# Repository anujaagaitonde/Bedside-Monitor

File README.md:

# LifeLine

LifeLine is a low-cost Internet-of-Things vital sign monitor with real-time illness prediction which allows doctors to monitor several patients at once from a remote location. Custom circuitry interfaces sensors to measure the patient's vital signs with any Raspberry Pi. Sensor data is displayed live on a bedside monitor and is live-streamed to a cloud-based database. A webapp allows doctors to monitor all their patients live, as well as viewing patient history over the past 24 hours. Sensor data is processed in real-time by a machine learning algorithm to detect and predict a critical event in the patient's status, which is relayed to the doctor via an instant notification in the webapp.

## Documentation

For further information about this project, visit our [wiki](https://github.com/anujaagaitonde/Bedside-Monitor/wiki):
* [1. Home](https://github.com/anujaagaitonde/Bedside-Monitor/wiki/1.-Home)
* [2. Product Design History](https://github.com/anujaagaitonde/Bedside-Monitor/wiki/2.-Product-Design-History)
* [2.1 Hardware and Firmware](https://github.com/anujaagaitonde/Bedside-Monitor/wiki/2.1-Hardware-and-Firmware)
* [2.2 Web App](https://github.com/anujaagaitonde/Bedside-Monitor/wiki/2.2-Web-App)
* [2.4 Deep Learning Model](https://github.com/anujaagaitonde/Bedside-Monitor/wiki/2.3-Deep-Learning-Model)
* [3. Meeting Records](https://github.com/anujaagaitonde/Bedside-Monitor/wiki/3.-Meeting-Records)
* [4. Innovation](https://github.com/anujaagaitonde/Bedside-Monitor/wiki/4.-Innovation)
* [5. Report of Ethical Consequences and Sustainability](https://github.com/anujaagaitonde/Bedside-Monitor/wiki/5.-Report-of-Ethical-Consequences-and-Sustainability)
* [6. Testing](https://github.com/anujaagaitonde/Bedside-Monitor/wiki/6.-Testing)
* [7. Getting Started](https://github.com/anujaagaitonde/Bedside-Monitor/wiki/7.-Getting-Started)

## About this Repository

* **[3D Printed Case:](https://github.com/anujaagaitonde/Bedside-Monitor/tree/master/3D%20Printed%20Case)** Contains 3D print and laser cut files for casing.
* **[GUI Mockups:](https://github.com/anujaagaitonde/Bedside-Monitor/tree/master/GUI%20Mockups)** Contains mockups for bedside LCD GUI.
* **[Hardware:](https://github.com/anujaagaitonde/Bedside-Monitor/tree/master/Hardware)** Contains PCB design files for PPG sensor and custom Raspberry Pi Hat.
* **[Machine Learning:](https://github.com/anujaagaitonde/Bedside-Monitor/tree/master/Machine%20Learning)** Contains illness prediction scripts.
* **[Pi:](https://github.com/anujaagaitonde/Bedside-Monitor/tree/master/Pi)** Contains the files to be run on the device Raspberry Pi and its associated libraries.
* **[Print:](https://github.com/anujaagaitonde/Bedside-Monitor/tree/master/Print)** Contains poster, leaflet and slideshow files used during demonstration.
* **[Web:](https://github.com/anujaagaitonde/Bedside-Monitor/tree/master/Web)** Contains webapp mockups and source files.

## The Project Team

* **Gasim Ahmed:** *Firmware and Machine Learning Developer*
* **Yasmin Baba:** *Hardware Designer*
* **Anuja Gaitonde:** *Web / GUI Developer and Print Promotion Designer*
* **Dayan Graham:** *Web / Cloud Developer and Casing Designer*
* **Prithvi Menon:** *Machine Learning Developer*
* **Omar Muttawa:** *Firmware Developer*

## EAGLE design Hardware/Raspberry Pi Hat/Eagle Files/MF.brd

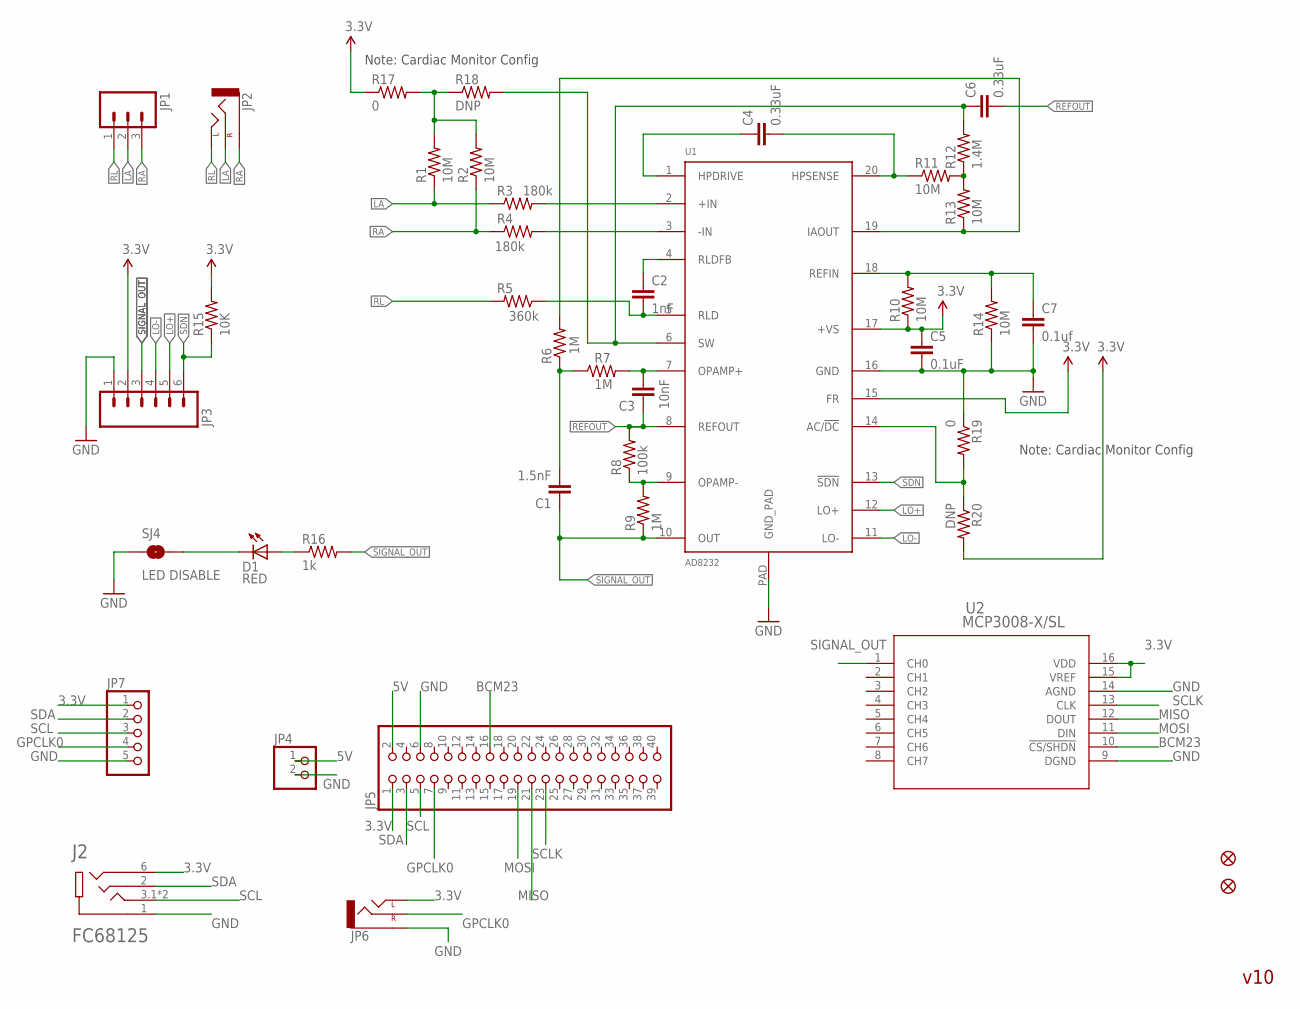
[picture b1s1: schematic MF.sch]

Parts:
C1: 1.5nF; 0603-CAP
C2: 1nF; 0603-CAP
C3: 10nF; 0603-CAP
C4, C6: 0.33uF; 0805
C5: 0.1uF; 0603-CAP
C7: 0.1uf; 0603-CAP
D1: RED; LED-0603
FID1, FID2: FIDUCIAL1X2; FIDUCIAL-1X2
J2: FC68125; CLIFF_FC68125
JP1: M03PTH; 1X03
JP2, JP6: AUDIO-JACKSMD2; AUDIO-JACK-3.5MM-SMD
JP3: M06SIP; 1X06
JP4: PINHD-1X2; 1X02
JP5: PINHD-2X20; 2X20
JP7: PINHD-1X5; 1X05
R1, R2, R10, R11, R13, R14: 10M; 0603-RES
R3, R4: 180k; 0603-RES
R5: 360k; 0603-RES
R6, R7, R9: 1M; 0603-RES
R8: 100k; 0603-RES
R12: 1.4M; 0603-RES
R15: 10K; 0603-RES
R16: 1k; 0603-RES
R17, R19: 0; 0603
R18, R20: DNP; 0603
SJ4: LED DISABLE; SJ_2S-TRACE
U1: AD8232; LFCSP_20
U2: MCP3008-X/SL; SOIC16-N_MC

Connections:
3.3V: C5.1, J2.6 (6SR), JP3.2, JP5.1, JP6.TIP (LEFT), JP7.1, R10.1, R15.2, R17.1, R20.2, U1.15 (FR), U1.17 (+VS), U2.15 (VREF), U2.16 (VDD)
5V: JP4.1, JP5.2
BCM23: JP5.16, U2.10 (!CS/SHDN)
GND: C5.2, C7.2, J2.1 (1S), JP3.1, JP4.2, JP5.6, JP6.SLEEVE, JP7.5, R14.1, R19.1, SJ4.1, U1.16 (GND), U1.PAD (GND_PAD), U2.9 (DGND), U2.14 (AGND)
GPCLK0: JP5.7, JP6.RING (RIGHT), JP7.4
LA: JP1.2, JP2.RING (RIGHT), R1.1, R3.1
LO+: JP3.5, U1.12 (LO+)
LO-: JP3.4, U1.11 (LO-)
MISO: JP5.21, U2.12 (DOUT)
MOSI: JP5.19, U2.11 (DIN)
unnamed: R3.2, U1.2 (+IN)
unnamed: R4.2, U1.3 (-IN)
unnamed: C3.2, R7.2, U1.7 (OPAMP+)
unnamed: C4.2, R11.1, U1.20 (HPSENSE)
unnamed: C7.1, R10.2, R14.2, U1.18 (REFIN)
unnamed: D1.A, R16.1
unnamed: R8.1, R9.2, U1.9 (OPAMP-)
unnamed: R6.2, R13.1, U1.19 (IAOUT)
unnamed: C1.2, R6.1, R7.1
unnamed: D1.C, SJ4.2
unnamed: R19.2, R20.1, U1.14 (AC/!DC)
unnamed: C4.1, U1.1 (HPDRIVE)
unnamed: R11.2, R12.1, R13.2
unnamed: C6.1, R12.2, R18.2, U1.6 (SW)
unnamed: C2.1, U1.4 (RLDFB)
unnamed: C2.2, R5.1, U1.5 (RLD)
unnamed: R1.2, R2.2, R17.2, R18.1
RA: JP1.3, JP2.SLEEVE, R2.1, R4.1
REFOUT: C3.1, C6.2, R8.2, U1.8 (REFOUT)
RL: JP1.1, JP2.TIP (LEFT), R5.2
SCL: J2.3.1 (3T), J2.3.2 (3T), JP5.5, JP7.3
SCLK: JP5.23, U2.13 (CLK)
SDA: J2.2 (2R), JP5.3, JP7.2
SDN: JP3.6, R15.1, U1.13 (!SDN)
SIGNAL_OUT: C1.1, JP3.3, R9.1, R16.2, U1.10 (OUT), U2.1 (CH0)

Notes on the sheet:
v10
Note: Cardiac Monitor Config

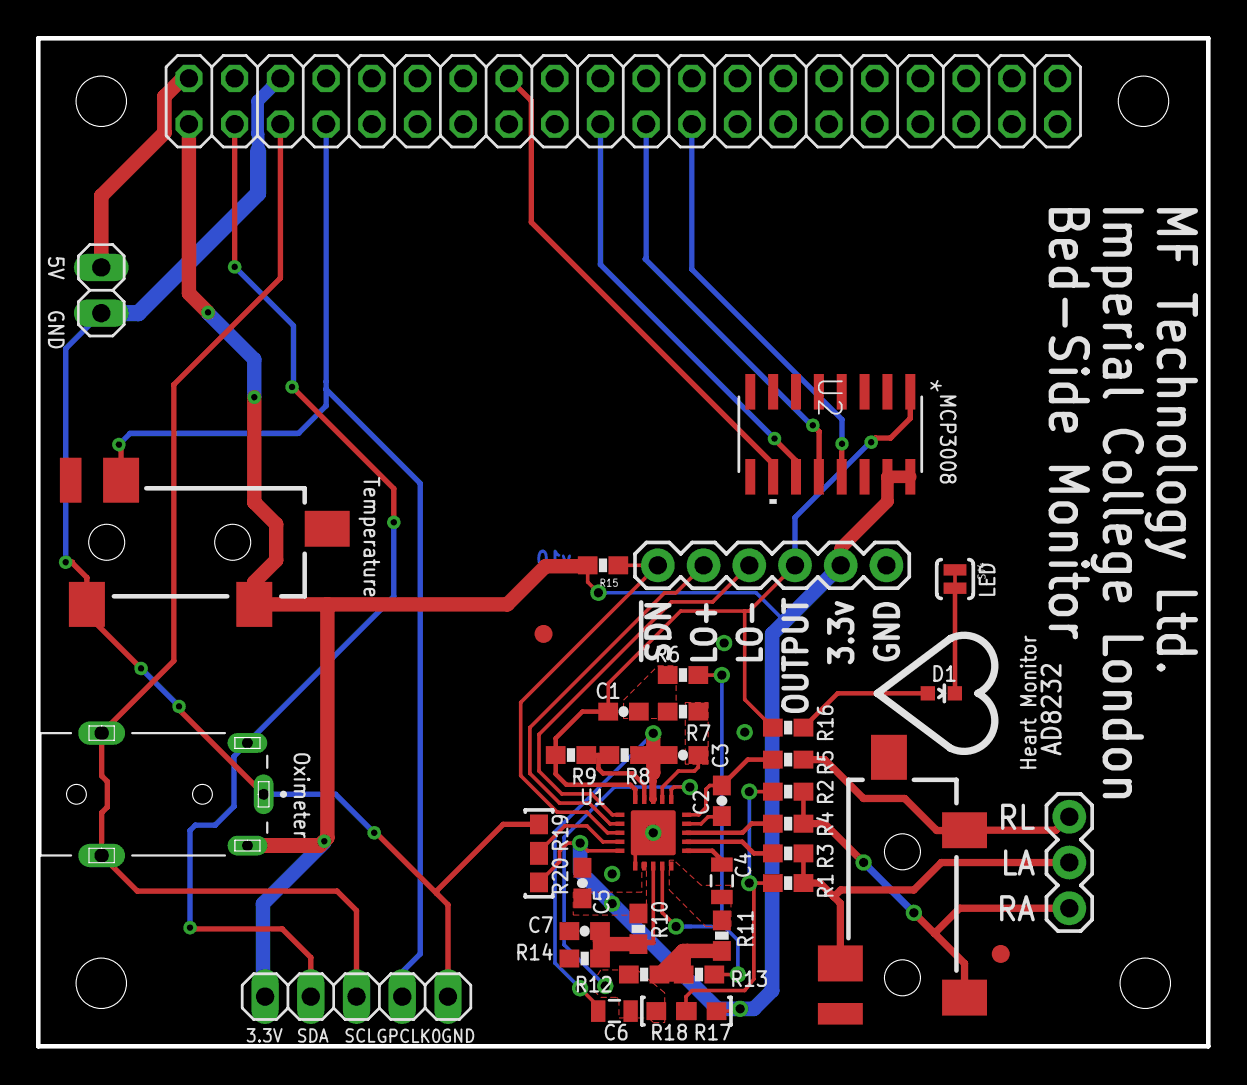
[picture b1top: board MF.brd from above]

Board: 2 copper layers, 65.0 x 56.0 mm, 41 parts (0 on the bottom side), 35 nets.

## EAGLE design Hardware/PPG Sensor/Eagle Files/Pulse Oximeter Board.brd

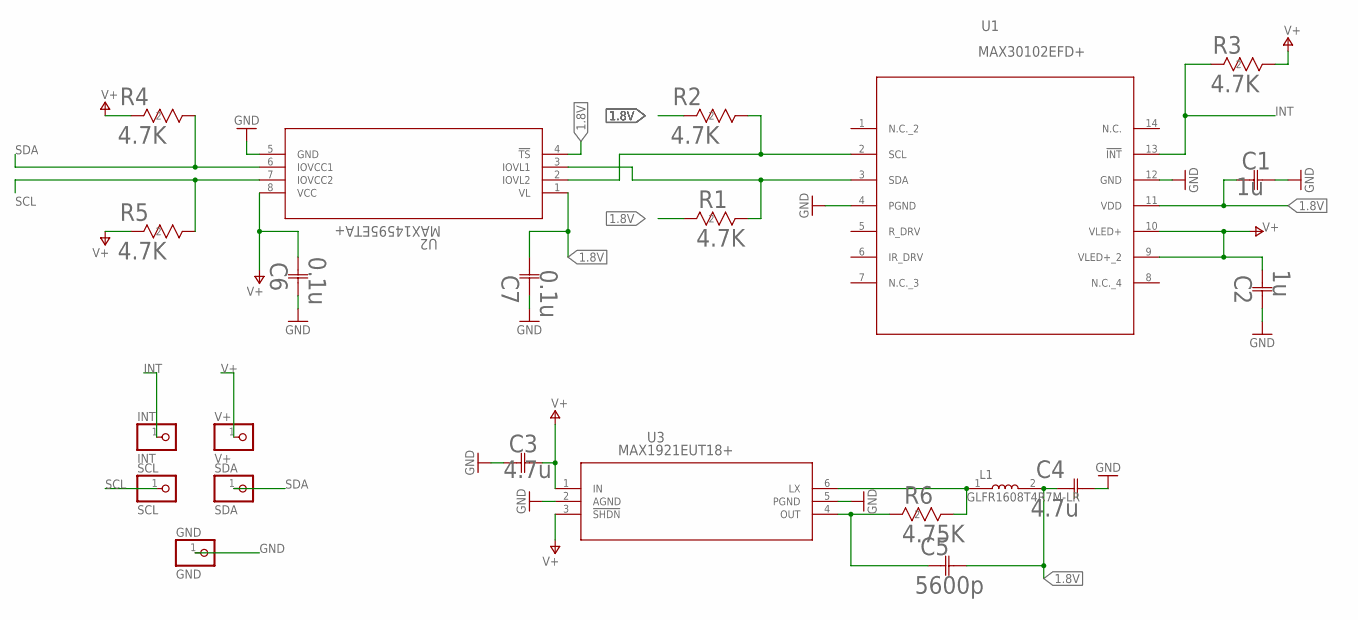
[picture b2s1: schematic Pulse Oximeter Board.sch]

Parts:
C1, C2: 1u; CAP_CHIP2_1X0P5
C3, C4: 4.7u; CAP_CHIP2_1X0P5
C5: 5600p; CAP_CHIP2_1X0P5
C6, C7: 0.1u; CAP_CHIP2_1X0P5
GND: GND; 1X01
INT: INT; 1X01
L1: GLFR1608T4R7M-LR; INDC1608X95N
R1, R2, R3, R4, R5: 4.7K; RES0402_CRG_TYCO
R6: 4.75K; RES0402_CRG_TYCO
SCL: SCL; 1X01
SDA: SDA; 1X01
U1: MAX30102EFD+; 21-0880B
U2: MAX14595ETA+; 21-0487A
U3: MAX1921EUT18+; 21-0058I
V+: V+; 1X01

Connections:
1.8V: C1.1, C4.1, C5.2, C7.1, L1.2, R1.2, R2.2, U1.11 (VDD), U2.1 (VL), U2.4 (!TS)
GND: C1.2, C2.2, C3.1, C4.2, C6.2, C7.2, GND.1, U1.4 (PGND), U1.12 (GND), U2.5 (GND), U3.2 (AGND), U3.5 (PGND)
INT: INT.1, R3.2, U1.13 (!INT)
unnamed: R2.1, U1.2 (SCL), U2.2 (IOVL2)
unnamed: L1.1, R6.1, U3.6 (LX)
unnamed: R1.1, U1.3 (SDA), U2.3 (IOVL1)
unnamed: C5.1, R6.2, U3.4 (OUT)
SCL: R5.1, SCL.1, U2.7 (IOVCC2)
SDA: R4.1, SDA.1, U2.6 (IOVCC1)
V+: C2.1, C3.2, C6.1, R3.1, R4.2, R5.2, U1.9 (VLED+_2), U1.10 (VLED+), U2.8 (VCC), U3.1 (IN), U3.3 (!SHDN), V+.1

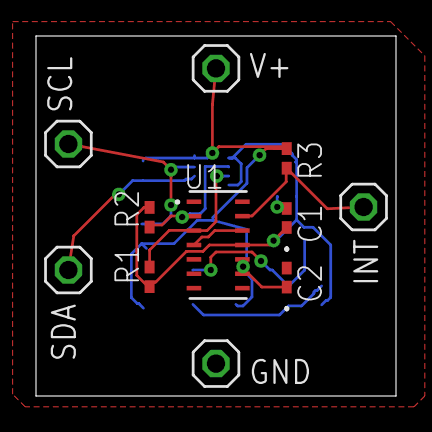
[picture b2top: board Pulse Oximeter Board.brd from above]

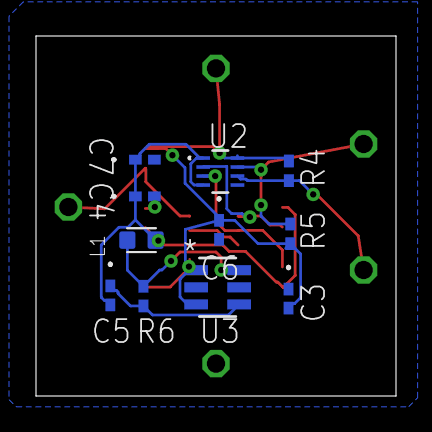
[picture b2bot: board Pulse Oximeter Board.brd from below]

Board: 2 copper layers, 20.0 x 20.0 mm, 22 parts (11 on the bottom side), 10 nets.

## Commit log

2019-05-17 Update patient dashboard
2019-05-17 responsive design updated
2019-05-17 load users from firebase
2019-05-17 add firebase for user list
2019-05-17 make patient dashboard redirect to live view
2019-05-20 starring capability added - needs checking
2019-05-20 added font support
2019-05-21 add starred functionality to database, filter screens by starred and critical
2019-05-21 login and signup pages added
2019-05-21 logout functionality added
2019-05-22 hook login and signup to firebase
2019-05-22 graph styling
2019-05-24 add history screen
2019-05-24 clean up live grapher code
2019-05-24 add pushing vector to live graph
2019-05-28 initial commit - ecg graph array added
2019-05-30 format patient view and add url, also add new patient screen
2019-05-30 added formatted graphs into tkinter gui
2019-05-31 added live data display fields, DB info and report button
2019-05-31 Added picode
2019-05-31 Added 20 second sample data of PPG signal
2019-05-31 make patient dashboard tabbed and add a loader
2019-06-03 first stage of implementation of gui
2019-06-03 fixed digitl value update on pi gui
2019-06-04 make tabbed
2019-06-05 Added gui_original and blitting example
2019-06-06 add loaders when fetching data and speed up data loading
2019-06-06 make gaps in history
2019-06-06 fixed GUI library (gui_copy) and example (gui_original)
2019-06-07 working version of gui + data for experiment
2019-06-10 latest
2019-06-10 update history grapher
2019-06-10 update db config
2019-06-10 change db location
2019-06-10 fix indentation
2019-06-10 fix indentation again
2019-06-10 fix indentation again in all files
2019-06-10 fix speech marks in firebase config
2019-06-10 added default ecg sampling rate in ecg processing
2019-06-10 updated multiprocessing
2019-06-10 add db lines
2019-06-10 add notification for emergencies
2019-06-11 add sp02 algorithm
2019-06-11 gui changes
2019-06-11 pulse block added to gui and resizing
2019-06-11 ui redesign
2019-06-11 fix sidebar ui
2019-06-11 fix firebase configs
2019-06-11 remove scipy dependency
2019-06-11 fix firebase config
2019-06-11 add ecg to history
2019-06-11 final changes of the night
2019-06-12 fix db glitch
2019-06-12 fix safari glitch and rm temp chart
2019-06-12 First working version
2019-06-12 firebase correction
2019-06-12 new ecg data
2019-06-12 working version without all db pushes
2019-06-13 We done out here
2019-06-20 last push before cleaning
2019-06-20 First stage of picode clean-up
2019-06-20 Rename picode/Testing/Libraries/PPG_lib/ecg_lib.py to picode/Testing/Libraries/ECG_lib/ecg_lib.py
2019-06-20 Rename picode/Testing/Libraries/PPG_lib/ecg_processing.py to picode/Testing/Libraries/ECGG_lib/ecg_processing.py
2019-06-20 Rename picode/Testing/Libraries/ECGG_lib/ecg_processing.py to picode/Testing/Libraries/ECG_lib/ecg_processing.py
2019-06-20 Rename picode/Libraries/PPG_lib/ecg_processing.py to picode/Libraries/ECG_lib/ecg_processing.py
2019-06-20 Rename picode/Libraries/PPG_lib/ecg_lib.py to picode/Libraries/ECG_lib/ecg_lib.py
2019-06-20 Rename picode/Libraries/PPG_lib/plotting.py to picode/Libraries/ECG_lib/plotting.py
2019-06-20 Rename picode/Testing/Libraries/PPG_lib/plotting.py to picode/Testing/Libraries/ECG_lib/plotting.py
2019-06-21 remove
2019-06-21 added web mockups and print media
2019-06-22 added config.txt
2019-06-22 added lifelinemain.service and setup.py for easy setup
2019-06-22 fixed setup.py
2019-06-22 changed from .call to .popen
2019-06-22 Popen
2019-06-22 changed to list of arguements
2019-06-22 fixed directory bug
2019-06-23 attempt to make temp modular
2019-06-23 duplicate bug
2019-06-23 second attempt at making temp modular
2019-06-24 Added hardware files
2019-06-24 added gui mockups
2019-06-24 Added Ml
2019-06-24 changed lifelinemain.service
2019-06-24 edited setup.py
2019-06-24 added print statements to setup.py
2019-06-24 picode/README.md updated from https://stackedit.io/
2019-06-25 Finally got lifelinemain.service and setup working correctly!
2019-06-26 add 3d printed files
2019-06-26 deleted duplicate lifelinemain.servce
2019-06-27 add slideshow
2019-06-27 rearrange repo
2019-06-27 update README.md according to wiki changes
2019-06-27 rename folders
2019-06-27 rename folders a
2019-06-27 update README.md to reflect folder name changes
2019-07-02 Added PyQtTest in Pi/Testing/ folder
2019-07-02 changes to test libs
2019-07-02 Added plot marker to PyQtTest
2019-07-02 Improved PyQtTest plotting speed
2019-07-03 Added PyQt update function timer
2019-07-03 Modified PyQt update function timer
2019-07-03 Slowed PyQtTest plotting for testing
2019-07-04 First Complete PyQtTest.py

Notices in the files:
parts and their libraries:
SparkFun-Aesthetics: Licensing: CC v3.0 Share-Alike You are welcome to use this library for commercial purposes.
